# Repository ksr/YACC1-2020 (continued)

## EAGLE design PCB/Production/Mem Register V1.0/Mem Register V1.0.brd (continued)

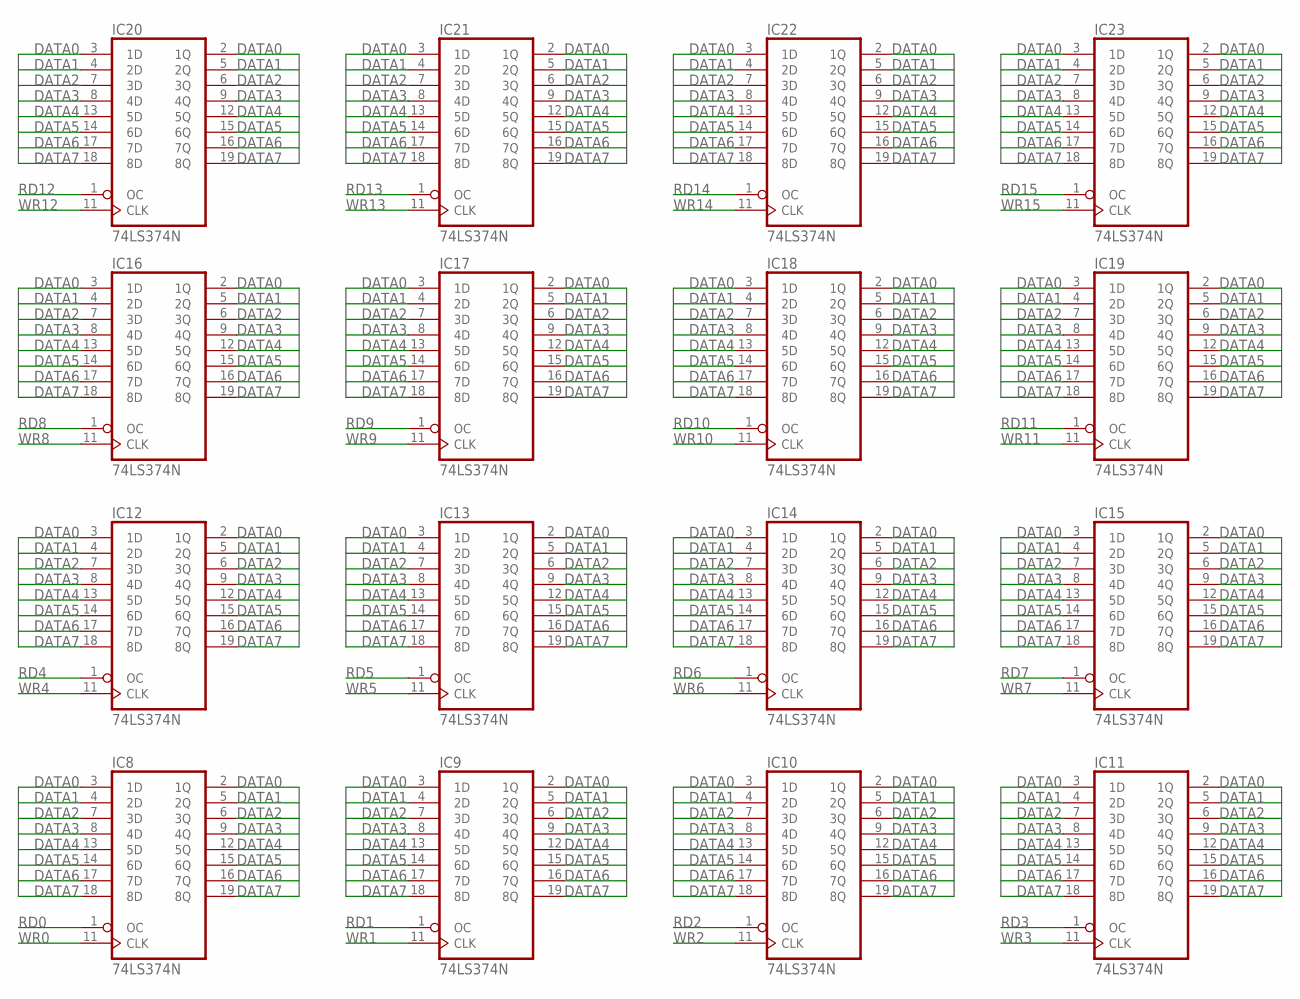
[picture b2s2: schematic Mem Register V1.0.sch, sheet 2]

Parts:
IC8, IC9, IC10, IC11, IC12, IC13, IC14, IC15, IC16, IC17, IC18, IC19, IC20, IC21, IC22, IC23: 74LS374N; DIL20

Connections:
DATA0: IC8.2 (1Q), IC8.3 (1D), IC9.2 (1Q), IC9.3 (1D), IC10.2 (1Q), IC10.3 (1D), IC11.2 (1Q), IC11.3 (1D), IC12.2 (1Q), IC12.3 (1D), IC13.2 (1Q), IC13.3 (1D), IC14.2 (1Q), IC14.3 (1D), IC15.2 (1Q), IC15.3 (1D), IC16.2 (1Q), IC16.3 (1D), IC17.2 (1Q), IC17.3 (1D), IC18.2 (1Q), IC18.3 (1D), IC19.2 (1Q), IC19.3 (1D), IC20.2 (1Q), IC20.3 (1D), IC21.2 (1Q), IC21.3 (1D), IC22.2 (1Q), IC22.3 (1D), IC23.2 (1Q), IC23.3 (1D); also elsewhere on the board
DATA1: IC8.4 (2D), IC8.5 (2Q), IC9.4 (2D), IC9.5 (2Q), IC10.4 (2D), IC10.5 (2Q), IC11.4 (2D), IC11.5 (2Q), IC12.4 (2D), IC12.5 (2Q), IC13.4 (2D), IC13.5 (2Q), IC14.4 (2D), IC14.5 (2Q), IC15.4 (2D), IC15.5 (2Q), IC16.4 (2D), IC16.5 (2Q), IC17.4 (2D), IC17.5 (2Q), IC18.4 (2D), IC18.5 (2Q), IC19.4 (2D), IC19.5 (2Q), IC20.4 (2D), IC20.5 (2Q), IC21.4 (2D), IC21.5 (2Q), IC22.4 (2D), IC22.5 (2Q), IC23.4 (2D), IC23.5 (2Q); also elsewhere on the board
DATA2: IC8.6 (3Q), IC8.7 (3D), IC9.6 (3Q), IC9.7 (3D), IC10.6 (3Q), IC10.7 (3D), IC11.6 (3Q), IC11.7 (3D), IC12.6 (3Q), IC12.7 (3D), IC13.6 (3Q), IC13.7 (3D), IC14.6 (3Q), IC14.7 (3D), IC15.6 (3Q), IC15.7 (3D), IC16.6 (3Q), IC16.7 (3D), IC17.6 (3Q), IC17.7 (3D), IC18.6 (3Q), IC18.7 (3D), IC19.6 (3Q), IC19.7 (3D), IC20.6 (3Q), IC20.7 (3D), IC21.6 (3Q), IC21.7 (3D), IC22.6 (3Q), IC22.7 (3D), IC23.6 (3Q), IC23.7 (3D); also elsewhere on the board
DATA3: IC8.8 (4D), IC8.9 (4Q), IC9.8 (4D), IC9.9 (4Q), IC10.8 (4D), IC10.9 (4Q), IC11.8 (4D), IC11.9 (4Q), IC12.8 (4D), IC12.9 (4Q), IC13.8 (4D), IC13.9 (4Q), IC14.8 (4D), IC14.9 (4Q), IC15.8 (4D), IC15.9 (4Q), IC16.8 (4D), IC16.9 (4Q), IC17.8 (4D), IC17.9 (4Q), IC18.8 (4D), IC18.9 (4Q), IC19.8 (4D), IC19.9 (4Q), IC20.8 (4D), IC20.9 (4Q), IC21.8 (4D), IC21.9 (4Q), IC22.8 (4D), IC22.9 (4Q), IC23.8 (4D), IC23.9 (4Q); also elsewhere on the board
DATA4: IC8.12 (5Q), IC8.13 (5D), IC9.12 (5Q), IC9.13 (5D), IC10.12 (5Q), IC10.13 (5D), IC11.12 (5Q), IC11.13 (5D), IC12.12 (5Q), IC12.13 (5D), IC13.12 (5Q), IC13.13 (5D), IC14.12 (5Q), IC14.13 (5D), IC15.12 (5Q), IC15.13 (5D), IC16.12 (5Q), IC16.13 (5D), IC17.12 (5Q), IC17.13 (5D), IC18.12 (5Q), IC18.13 (5D), IC19.12 (5Q), IC19.13 (5D), IC20.12 (5Q), IC20.13 (5D), IC21.12 (5Q), IC21.13 (5D), IC22.12 (5Q), IC22.13 (5D), IC23.12 (5Q), IC23.13 (5D); also elsewhere on the board
DATA5: IC8.14 (6D), IC8.15 (6Q), IC9.14 (6D), IC9.15 (6Q), IC10.14 (6D), IC10.15 (6Q), IC11.14 (6D), IC11.15 (6Q), IC12.14 (6D), IC12.15 (6Q), IC13.14 (6D), IC13.15 (6Q), IC14.14 (6D), IC14.15 (6Q), IC15.14 (6D), IC15.15 (6Q), IC16.14 (6D), IC16.15 (6Q), IC17.14 (6D), IC17.15 (6Q), IC18.14 (6D), IC18.15 (6Q), IC19.14 (6D), IC19.15 (6Q), IC20.14 (6D), IC20.15 (6Q), IC21.14 (6D), IC21.15 (6Q), IC22.14 (6D), IC22.15 (6Q), IC23.14 (6D), IC23.15 (6Q); also elsewhere on the board
DATA6: IC8.16 (7Q), IC8.17 (7D), IC9.16 (7Q), IC9.17 (7D), IC10.16 (7Q), IC10.17 (7D), IC11.16 (7Q), IC11.17 (7D), IC12.16 (7Q), IC12.17 (7D), IC13.16 (7Q), IC13.17 (7D), IC14.16 (7Q), IC14.17 (7D), IC15.16 (7Q), IC15.17 (7D), IC16.16 (7Q), IC16.17 (7D), IC17.16 (7Q), IC17.17 (7D), IC18.16 (7Q), IC18.17 (7D), IC19.16 (7Q), IC19.17 (7D), IC20.16 (7Q), IC20.17 (7D), IC21.16 (7Q), IC21.17 (7D), IC22.16 (7Q), IC22.17 (7D), IC23.16 (7Q), IC23.17 (7D); also elsewhere on the board
DATA7: IC8.18 (8D), IC8.19 (8Q), IC9.18 (8D), IC9.19 (8Q), IC10.18 (8D), IC10.19 (8Q), IC11.18 (8D), IC11.19 (8Q), IC12.18 (8D), IC12.19 (8Q), IC13.18 (8D), IC13.19 (8Q), IC14.18 (8D), IC14.19 (8Q), IC15.18 (8D), IC15.19 (8Q), IC16.18 (8D), IC16.19 (8Q), IC17.18 (8D), IC17.19 (8Q), IC18.18 (8D), IC18.19 (8Q), IC19.18 (8D), IC19.19 (8Q), IC20.18 (8D), IC20.19 (8Q), IC21.18 (8D), IC21.19 (8Q), IC22.18 (8D), IC22.19 (8Q), IC23.18 (8D), IC23.19 (8Q); also elsewhere on the board
GND: IC8.10 (GND), IC9.10 (GND), IC10.10 (GND), IC11.10 (GND), IC12.10 (GND), IC13.10 (GND), IC14.10 (GND), IC15.10 (GND), IC16.10 (GND), IC17.10 (GND), IC18.10 (GND), IC19.10 (GND), IC20.10 (GND), IC21.10 (GND), IC22.10 (GND), IC23.10 (GND); also elsewhere on the board
RD0: IC8.1 (OC); also elsewhere on the board
RD1: IC9.1 (OC); also elsewhere on the board
RD2: IC10.1 (OC); also elsewhere on the board
RD3: IC11.1 (OC); also elsewhere on the board
RD4: IC12.1 (OC); also elsewhere on the board
RD5: IC13.1 (OC); also elsewhere on the board
RD6: IC14.1 (OC); also elsewhere on the board
RD7: IC15.1 (OC); also elsewhere on the board
RD8: IC16.1 (OC); also elsewhere on the board
RD9: IC17.1 (OC); also elsewhere on the board
RD10: IC18.1 (OC); also elsewhere on the board
RD11: IC19.1 (OC); also elsewhere on the board
RD12: IC20.1 (OC); also elsewhere on the board
RD13: IC21.1 (OC); also elsewhere on the board
RD14: IC22.1 (OC); also elsewhere on the board
RD15: IC23.1 (OC); also elsewhere on the board
VCC: IC8.20 (VCC), IC9.20 (VCC), IC10.20 (VCC), IC11.20 (VCC), IC12.20 (VCC), IC13.20 (VCC), IC14.20 (VCC), IC15.20 (VCC), IC16.20 (VCC), IC17.20 (VCC), IC18.20 (VCC), IC19.20 (VCC), IC20.20 (VCC), IC21.20 (VCC), IC22.20 (VCC), IC23.20 (VCC); also elsewhere on the board
WR0: IC8.11 (CLK); also elsewhere on the board
WR1: IC9.11 (CLK); also elsewhere on the board
WR2: IC10.11 (CLK); also elsewhere on the board
WR3: IC11.11 (CLK); also elsewhere on the board
WR4: IC12.11 (CLK); also elsewhere on the board
WR5: IC13.11 (CLK); also elsewhere on the board
WR6: IC14.11 (CLK); also elsewhere on the board
WR7: IC15.11 (CLK); also elsewhere on the board
WR8: IC16.11 (CLK); also elsewhere on the board
WR9: IC17.11 (CLK); also elsewhere on the board
WR10: IC18.11 (CLK); also elsewhere on the board
WR11: IC19.11 (CLK); also elsewhere on the board
WR12: IC20.11 (CLK); also elsewhere on the board
WR13: IC21.11 (CLK); also elsewhere on the board
WR14: IC22.11 (CLK); also elsewhere on the board
WR15: IC23.11 (CLK); also elsewhere on the board

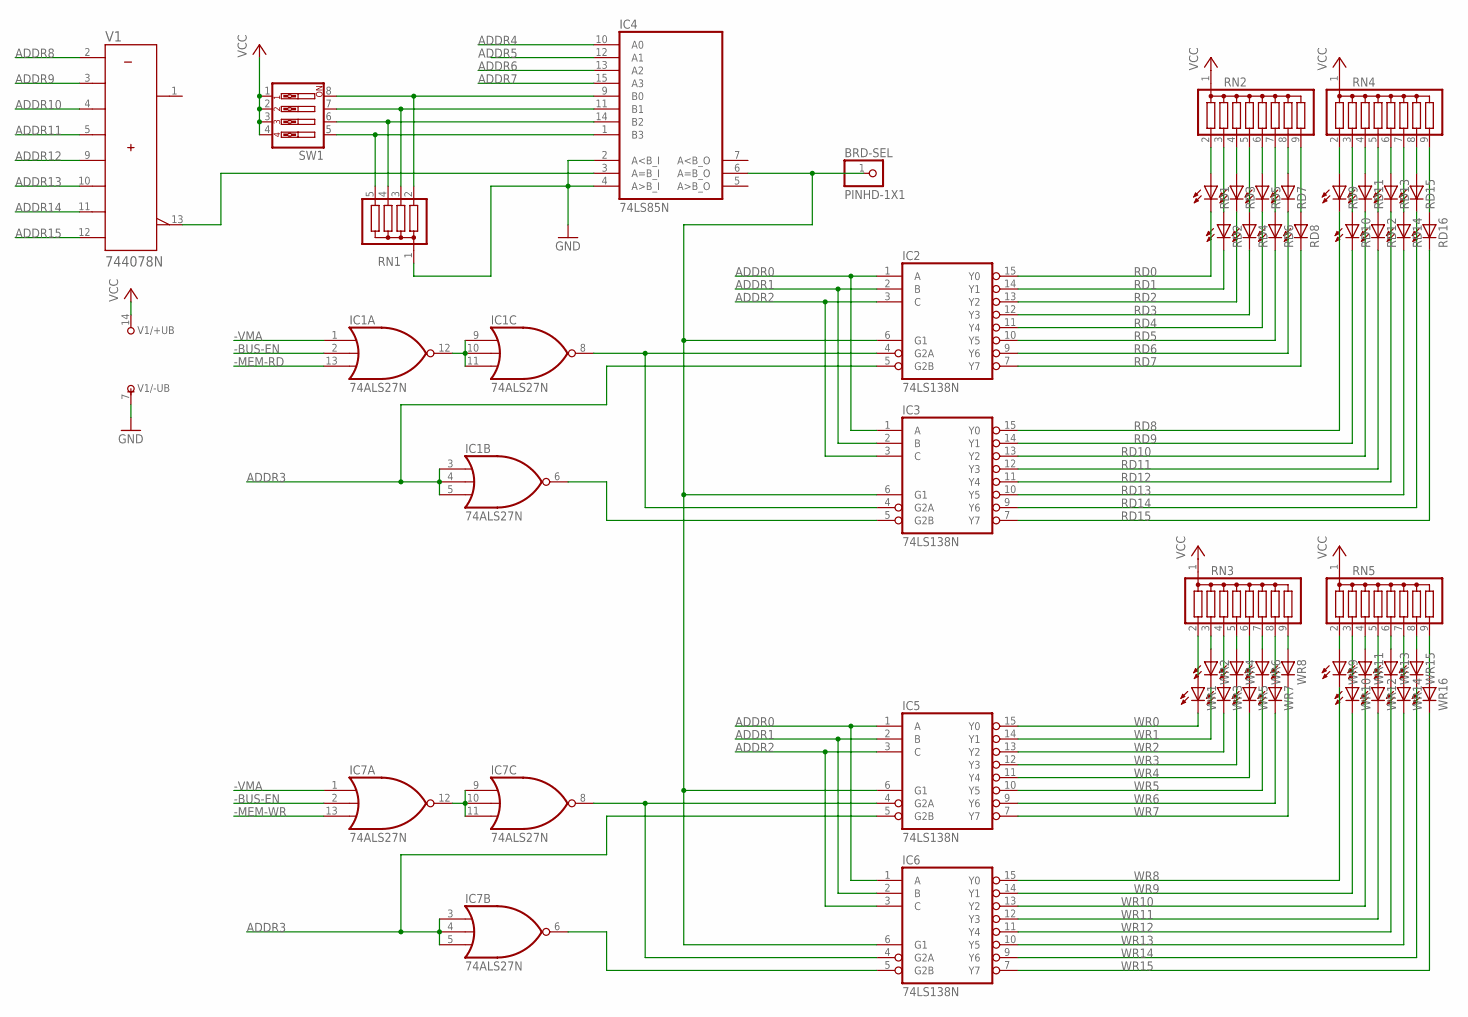
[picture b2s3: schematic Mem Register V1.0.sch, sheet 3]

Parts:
BRD-SEL: PINHD-1X1; 1X01
IC1, IC7: 74ALS27N; DIL14
IC2, IC3, IC5, IC6: 74LS138N; DIL16
IC4: 74LS85N; DIL16
RD1, RD2, RD3, RD4, RD5, RD6, RD7, RD8, RD9, RD10, RD11, RD12, RD13, RD14, RD15, RD16: LED3MM
RN1: G04R; SIL5
RN2, RN3, RN4, RN5: G08R; SIL9
SW1: SW_DIP-4; EDG-04
V1: 744078N; DIL14
WR1, WR2, WR3, WR4, WR5, WR6, WR7, WR8, WR9, WR10, WR11, WR12, WR13, WR14, WR15, WR16: LED3MM

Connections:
-BUS-EN: IC1.2 (I1), IC7.2 (I1); also elsewhere on the board
-MEM-RD: IC1.13 (I2); also elsewhere on the board
-MEM-WR: IC7.13 (I2); also elsewhere on the board
-VMA: IC1.1 (I0), IC7.1 (I0); also elsewhere on the board
ADDR0: IC2.1 (A), IC3.1 (A), IC5.1 (A), IC6.1 (A); also elsewhere on the board
ADDR1: IC2.2 (B), IC3.2 (B), IC5.2 (B), IC6.2 (B); also elsewhere on the board
ADDR2: IC2.3 (C), IC3.3 (C), IC5.3 (C), IC6.3 (C); also elsewhere on the board
ADDR3: IC1.3 (I0), IC1.4 (I1), IC1.5 (I2), IC2.5 (G2B), IC5.5 (G2B), IC7.3 (I0), IC7.4 (I1), IC7.5 (I2); also elsewhere on the board
ADDR4: IC4.10 (A0); also elsewhere on the board
ADDR5: IC4.12 (A1); also elsewhere on the board
ADDR6: IC4.13 (A2); also elsewhere on the board
ADDR7: IC4.15 (A3); also elsewhere on the board
ADDR8: V1.2 (A); also elsewhere on the board
ADDR9: V1.3 (B); also elsewhere on the board
ADDR10: V1.4 (C); also elsewhere on the board
ADDR11: V1.5 (D); also elsewhere on the board
ADDR12: V1.9 (E); also elsewhere on the board
ADDR13: V1.10 (F); also elsewhere on the board
ADDR14: V1.11 (G); also elsewhere on the board
ADDR15: V1.12 (H); also elsewhere on the board
GND: IC1.7 (GND), IC2.8 (GND), IC3.8 (GND), IC4.2 (A<B_I), IC4.4 (A>B_I), IC4.8 (GND), IC5.8 (GND), IC6.8 (GND), IC7.7 (GND), RN1.1, V1.7 (-UB); also elsewhere on the board
unnamed: RD1.A, RN2.2
unnamed: IC7.9 (I0), IC7.10 (I1), IC7.11 (I2), IC7.12 (O)
unnamed: IC6.5 (G2B), IC7.6 (O)
unnamed: IC5.4 (G2A), IC6.4 (G2A), IC7.8 (O)
unnamed: RD3.A, RN2.4
unnamed: BRD-SEL.1, IC2.6 (G1), IC3.6 (G1), IC4.6 (A=B_O), IC5.6 (G1), IC6.6 (G1)
unnamed: RD2.A, RN2.3
unnamed: IC4.3 (A=B_I), V1.13 (W)
unnamed: RD9.A, RN4.2
unnamed: RD4.A, RN2.5
unnamed: RD5.A, RN2.6
unnamed: RD7.A, RN2.8
unnamed: RD8.A, RN2.9
unnamed: RD6.A, RN2.7
unnamed: RD10.A, RN4.3
unnamed: RD11.A, RN4.4
unnamed: RD12.A, RN4.5
unnamed: IC1.9 (I0), IC1.10 (I1), IC1.11 (I2), IC1.12 (O)
unnamed: RD13.A, RN4.6
unnamed: RD14.A, RN4.7
unnamed: RD15.A, RN4.8
unnamed: RD16.A, RN4.9
unnamed: RN3.2, WR1.A
unnamed: RN3.3, WR2.A
unnamed: RN3.4, WR3.A
unnamed: RN3.5, WR4.A
unnamed: IC4.9 (B0), RN1.2, SW1.8
unnamed: RN3.7, WR6.A
unnamed: RN3.6, WR5.A
unnamed: RN3.8, WR7.A
unnamed: RN3.9, WR8.A
unnamed: RN5.2, WR9.A
unnamed: RN5.4, WR11.A
unnamed: RN5.6, WR13.A
unnamed: RN5.8, WR15.A
unnamed: IC1.6 (O), IC3.5 (G2B)
unnamed: RN5.9, WR16.A
unnamed: RN5.7, WR14.A
unnamed: RN5.5, WR12.A
unnamed: RN5.3, WR10.A
unnamed: IC4.11 (B1), RN1.3, SW1.7
unnamed: IC4.14 (B2), RN1.4, SW1.6
unnamed: IC4.1 (B3), RN1.5, SW1.5
unnamed: IC1.8 (O), IC2.4 (G2A), IC3.4 (G2A)
RD0: IC2.15 (Y0), RD1.K (C); also elsewhere on the board
RD1: IC2.14 (Y1), RD2.K (C); also elsewhere on the board
RD2: IC2.13 (Y2), RD3.K (C); also elsewhere on the board
RD3: IC2.12 (Y3), RD4.K (C); also elsewhere on the board
RD4: IC2.11 (Y4), RD5.K (C); also elsewhere on the board
RD5: IC2.10 (Y5), RD6.K (C); also elsewhere on the board
RD6: IC2.9 (Y6), RD7.K (C); also elsewhere on the board
RD7: IC2.7 (Y7), RD8.K (C); also elsewhere on the board
RD8: IC3.15 (Y0), RD9.K (C); also elsewhere on the board
RD9: IC3.14 (Y1), RD10.K (C); also elsewhere on the board
RD10: IC3.13 (Y2), RD11.K (C); also elsewhere on the board
RD11: IC3.12 (Y3), RD12.K (C); also elsewhere on the board
RD12: IC3.11 (Y4), RD13.K (C); also elsewhere on the board
RD13: IC3.10 (Y5), RD14.K (C); also elsewhere on the board
RD14: IC3.9 (Y6), RD15.K (C); also elsewhere on the board
RD15: IC3.7 (Y7), RD16.K (C); also elsewhere on the board
VCC: IC1.14 (VCC), IC2.16 (VCC), IC3.16 (VCC), IC4.16 (VCC), IC5.16 (VCC), IC6.16 (VCC), IC7.14 (VCC), RN2.1, RN3.1, RN4.1, RN5.1, SW1.1, SW1.2, SW1.3, SW1.4, V1.14 (+UB); also elsewhere on the board
WR0: IC5.15 (Y0), WR1.K (C); also elsewhere on the board
WR1: IC5.14 (Y1), WR2.K (C); also elsewhere on the board
WR2: IC5.13 (Y2), WR3.K (C); also elsewhere on the board
WR3: IC5.12 (Y3), WR4.K (C); also elsewhere on the board
WR4: IC5.11 (Y4), WR5.K (C); also elsewhere on the board
WR5: IC5.10 (Y5), WR6.K (C); also elsewhere on the board
WR6: IC5.9 (Y6), WR7.K (C); also elsewhere on the board
WR7: IC5.7 (Y7), WR8.K (C); also elsewhere on the board
WR8: IC6.15 (Y0), WR9.K (C); also elsewhere on the board
WR9: IC6.14 (Y1), WR10.K (C); also elsewhere on the board
WR10: IC6.13 (Y2), WR11.K (C); also elsewhere on the board
WR11: IC6.12 (Y3), WR12.K (C); also elsewhere on the board
WR12: IC6.11 (Y4), WR13.K (C); also elsewhere on the board
WR13: IC6.10 (Y5), WR14.K (C); also elsewhere on the board
WR14: IC6.9 (Y6), WR15.K (C); also elsewhere on the board
WR15: IC6.7 (Y7), WR16.K (C); also elsewhere on the board

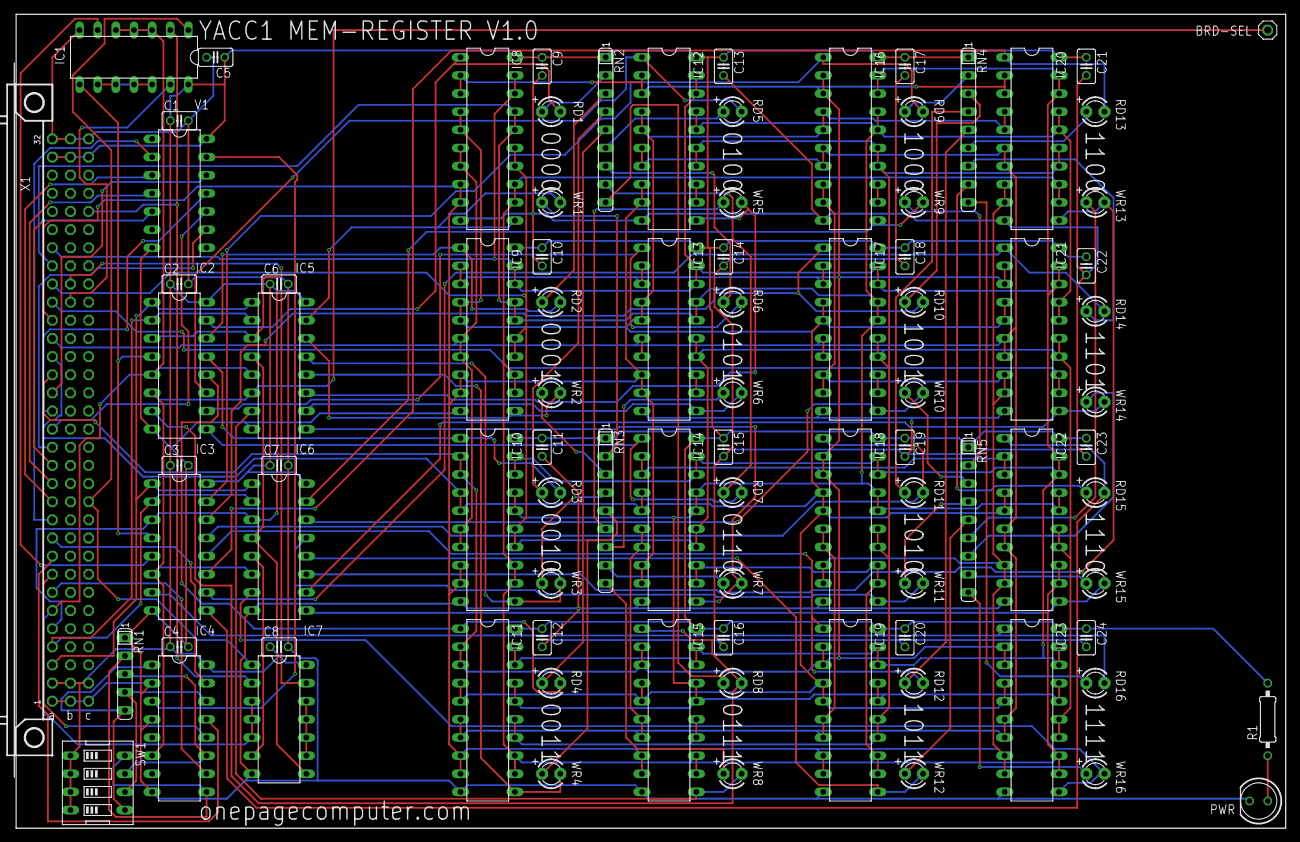
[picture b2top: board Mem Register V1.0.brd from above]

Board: 2 copper layers, 177.8 x 114.0 mm, 90 parts (0 on the bottom side), 107 nets.

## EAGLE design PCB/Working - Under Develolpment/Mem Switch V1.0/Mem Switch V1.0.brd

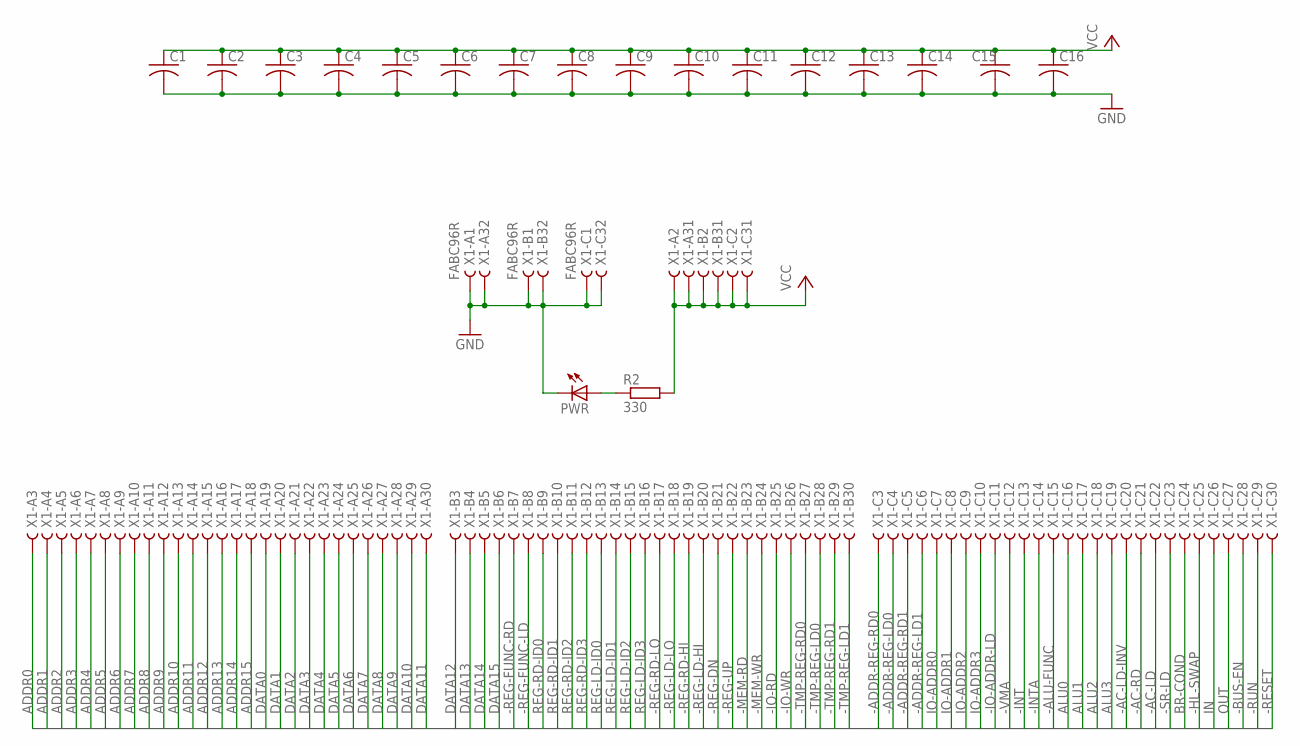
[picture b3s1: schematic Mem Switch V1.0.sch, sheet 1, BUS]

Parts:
C1, C2, C3, C4, C5, C6, C7, C8, C9, C10, C11, C12, C13, C14, C15, C16: C-US025-025X050; C025-025X050
PWR: LED5MM
R2: 330; 0207/10
X1: FABC96R

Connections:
-AC-LD: X1.C22
-AC-LD-INV: X1.C20
-AC-RD: X1.C21
-ADDR-REG-LD0: X1.C4
-ADDR-REG-LD1: X1.C6
-ADDR-REG-RD0: X1.C3
-ADDR-REG-RD1: X1.C5
-ALU-FUNC: X1.C15
-BUS-EN: X1.C28; also elsewhere on the board
-HL-SWAP: X1.C25
-INT: X1.C13
-INTA: X1.C14
-IO-ADDR-LD: X1.C11
-IO-RD: X1.B25
-IO-WR: X1.B26
-MEM-RD: X1.B23; also elsewhere on the board
-MEM-WR: X1.B24
-REG-DN: X1.B21
-REG-FUNC-LD: X1.B8
-REG-FUNC-RD: X1.B7
-REG-LD-HI: X1.B20
-REG-LD-LO: X1.B18
-REG-RD-HI: X1.B19
-REG-RD-LO: X1.B17
-REG-UP: X1.B22
-RESET: X1.C30
-RUN: X1.C29
-SR-LD: X1.C23
-TMP-REG-LD0: X1.B28
-TMP-REG-LD1: X1.B30
-TMP-REG-RD0: X1.B27
-TMP-REG-RD1: X1.B29
-VMA: X1.C12; also elsewhere on the board
ADDR0: X1.A3; also elsewhere on the board
ADDR1: X1.A4; also elsewhere on the board
ADDR2: X1.A5; also elsewhere on the board
ADDR3: X1.A6; also elsewhere on the board
ADDR4: X1.A7; also elsewhere on the board
ADDR5: X1.A8; also elsewhere on the board
ADDR6: X1.A9
ADDR7: X1.A10
ADDR8: X1.A11; also elsewhere on the board
ADDR9: X1.A12; also elsewhere on the board
ADDR10: X1.A13; also elsewhere on the board
ADDR11: X1.A14; also elsewhere on the board
ADDR12: X1.A15; also elsewhere on the board
ADDR13: X1.A16; also elsewhere on the board
ADDR14: X1.A17; also elsewhere on the board
ADDR15: X1.A18; also elsewhere on the board
ALU0: X1.C16
ALU1: X1.C17
ALU2: X1.C18
ALU3: X1.C19
BR-COND: X1.C24
DATA0: X1.A19; also elsewhere on the board
DATA1: X1.A20; also elsewhere on the board
DATA2: X1.A21; also elsewhere on the board
DATA3: X1.A22; also elsewhere on the board
DATA4: X1.A23; also elsewhere on the board
DATA5: X1.A24; also elsewhere on the board
DATA6: X1.A25; also elsewhere on the board
DATA7: X1.A26; also elsewhere on the board
DATA8: X1.A27
DATA9: X1.A28
DATA10: X1.A29
DATA11: X1.A30
DATA12: X1.B3
DATA13: X1.B4
DATA14: X1.B5
DATA15: X1.B6
GND: C1.2, C2.2, C3.2, C4.2, C5.2, C6.2, C7.2, C8.2, C9.2, C10.2, C11.2, C12.2, C13.2, C14.2, C15.2, C16.2, PWR.K (C), X1.A1, X1.A32, X1.B1, X1.B32, X1.C1, X1.C32; also elsewhere on the board
IN: X1.C26
IO-ADDR0: X1.C7
IO-ADDR1: X1.C8
IO-ADDR2: X1.C9
IO-ADDR3: X1.C10
unnamed: PWR.A, R2.1
OUT: X1.C27
REG-LD-ID0: X1.B13
REG-LD-ID1: X1.B14
REG-LD-ID2: X1.B15
REG-LD-ID3: X1.B16
REG-RD-ID0: X1.B9
REG-RD-ID1: X1.B10
REG-RD-ID2: X1.B11
REG-RD-ID3: X1.B12
VCC: C1.1, C2.1, C3.1, C4.1, C5.1, C6.1, C7.1, C8.1, C9.1, C10.1, C11.1, C12.1, C13.1, C14.1, C15.1, C16.1, R2.2, X1.A2, X1.A31, X1.B2, X1.B31, X1.C2, X1.C31; also elsewhere on the board

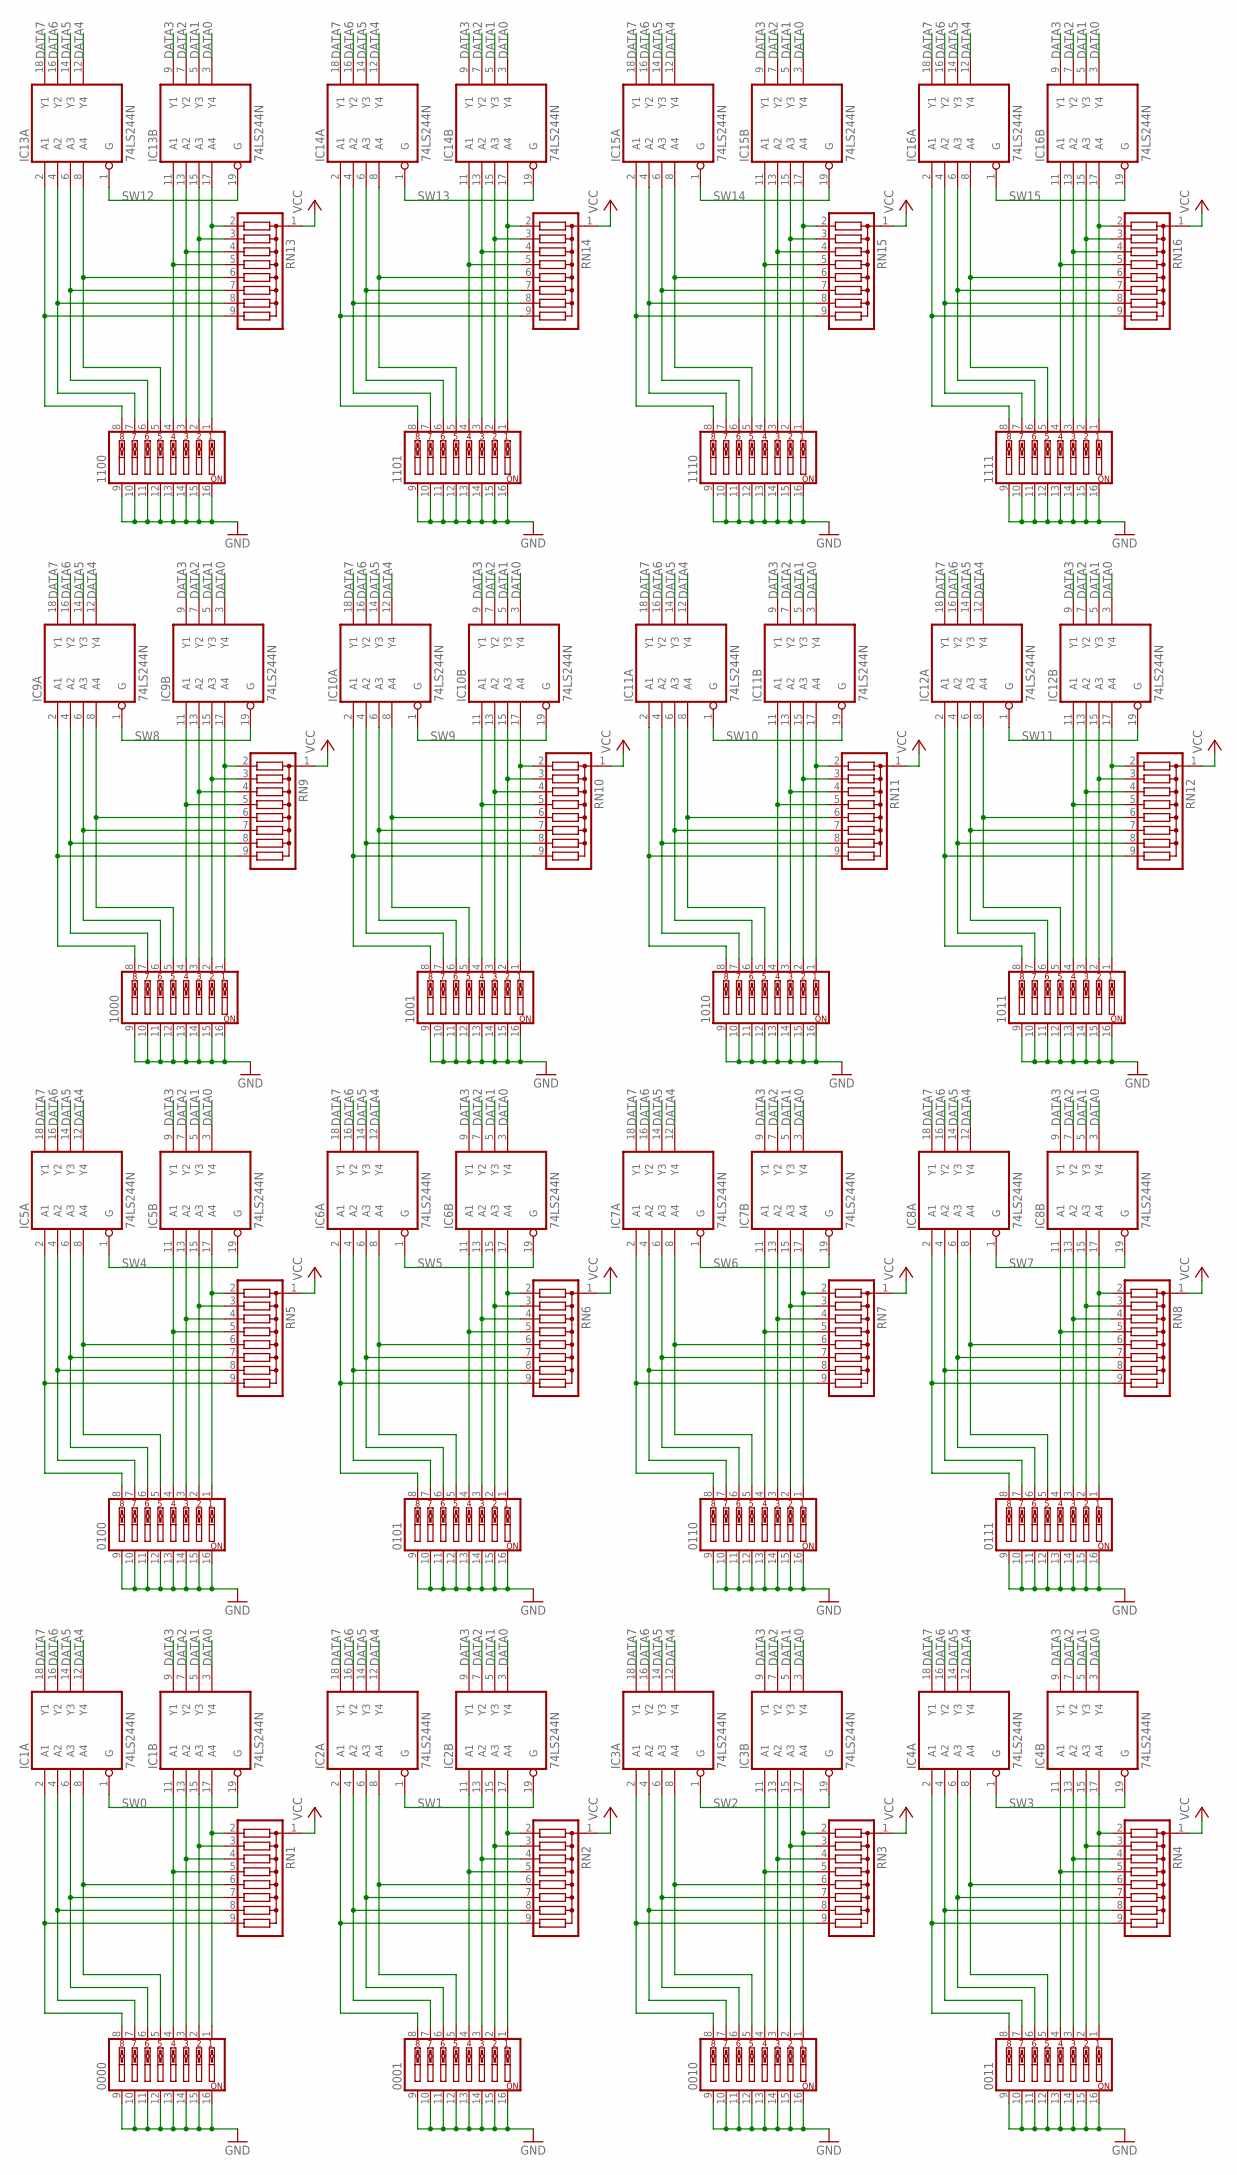
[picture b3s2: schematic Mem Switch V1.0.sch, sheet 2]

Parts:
0000, 0001, 0010, 0011, 0100, 0101, 0110, 0111, 1000, 1001, 1010, 1011, 1100, 1101, 1110, 1111: SW_DIP-8; EDG-08
IC1, IC2, IC3, IC4, IC5, IC6, IC7, IC8, IC9, IC10, IC11, IC12, IC13, IC14, IC15, IC16: 74LS244N; DIL20
RN1, RN2, RN3, RN4, RN5, RN6, RN7, RN8, RN9, RN10, RN11, RN12, RN13, RN14, RN15, RN16: G08R; SIL9

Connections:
DATA0: IC1.3 (Y4), IC2.3 (Y4), IC3.3 (Y4), IC4.3 (Y4), IC5.3 (Y4), IC6.3 (Y4), IC7.3 (Y4), IC8.3 (Y4), IC9.3 (Y4), IC10.3 (Y4), IC11.3 (Y4), IC12.3 (Y4), IC13.3 (Y4), IC14.3 (Y4), IC15.3 (Y4), IC16.3 (Y4); also elsewhere on the board
DATA1: IC1.5 (Y3), IC2.5 (Y3), IC3.5 (Y3), IC4.5 (Y3), IC5.5 (Y3), IC6.5 (Y3), IC7.5 (Y3), IC8.5 (Y3), IC9.5 (Y3), IC10.5 (Y3), IC11.5 (Y3), IC12.5 (Y3), IC13.5 (Y3), IC14.5 (Y3), IC15.5 (Y3), IC16.5 (Y3); also elsewhere on the board
DATA2: IC1.7 (Y2), IC2.7 (Y2), IC3.7 (Y2), IC4.7 (Y2), IC5.7 (Y2), IC6.7 (Y2), IC7.7 (Y2), IC8.7 (Y2), IC9.7 (Y2), IC10.7 (Y2), IC11.7 (Y2), IC12.7 (Y2), IC13.7 (Y2), IC14.7 (Y2), IC15.7 (Y2), IC16.7 (Y2); also elsewhere on the board
DATA3: IC1.9 (Y1), IC2.9 (Y1), IC3.9 (Y1), IC4.9 (Y1), IC5.9 (Y1), IC6.9 (Y1), IC7.9 (Y1), IC8.9 (Y1), IC9.9 (Y1), IC10.9 (Y1), IC11.9 (Y1), IC12.9 (Y1), IC13.9 (Y1), IC14.9 (Y1), IC15.9 (Y1), IC16.9 (Y1); also elsewhere on the board
DATA4: IC1.12 (Y4), IC2.12 (Y4), IC3.12 (Y4), IC4.12 (Y4), IC5.12 (Y4), IC6.12 (Y4), IC7.12 (Y4), IC8.12 (Y4), IC9.12 (Y4), IC10.12 (Y4), IC11.12 (Y4), IC12.12 (Y4), IC13.12 (Y4), IC14.12 (Y4), IC15.12 (Y4), IC16.12 (Y4); also elsewhere on the board
DATA5: IC1.14 (Y3), IC2.14 (Y3), IC3.14 (Y3), IC4.14 (Y3), IC5.14 (Y3), IC6.14 (Y3), IC7.14 (Y3), IC8.14 (Y3), IC9.14 (Y3), IC10.14 (Y3), IC11.14 (Y3), IC12.14 (Y3), IC13.14 (Y3), IC14.14 (Y3), IC15.14 (Y3), IC16.14 (Y3); also elsewhere on the board
DATA6: IC1.16 (Y2), IC2.16 (Y2), IC3.16 (Y2), IC4.16 (Y2), IC5.16 (Y2), IC6.16 (Y2), IC7.16 (Y2), IC8.16 (Y2), IC9.16 (Y2), IC10.16 (Y2), IC11.16 (Y2), IC12.16 (Y2), IC13.16 (Y2), IC14.16 (Y2), IC15.16 (Y2), IC16.16 (Y2); also elsewhere on the board
DATA7: IC1.18 (Y1), IC2.18 (Y1), IC3.18 (Y1), IC4.18 (Y1), IC5.18 (Y1), IC6.18 (Y1), IC7.18 (Y1), IC8.18 (Y1), IC9.18 (Y1), IC10.18 (Y1), IC11.18 (Y1), IC12.18 (Y1), IC13.18 (Y1), IC14.18 (Y1), IC15.18 (Y1), IC16.18 (Y1); also elsewhere on the board
GND: 0000.9, 0000.10, 0000.11, 0000.12, 0000.13, 0000.14, 0000.15, 0000.16, 0001.9, 0001.10, 0001.11, 0001.12, 0001.13, 0001.14, 0001.15, 0001.16, 0010.9, 0010.10, 0010.11, 0010.12, 0010.13, 0010.14, 0010.15, 0010.16, 0011.9, 0011.10, 0011.11, 0011.12, 0011.13, 0011.14, 0011.15, 0011.16, 0100.9, 0100.10, 0100.11, 0100.12, 0100.13, 0100.14, 0100.15, 0100.16, 0101.9, 0101.10, 0101.11, 0101.12, 0101.13, 0101.14, 0101.15, 0101.16, 0110.9, 0110.10, 0110.11, 0110.12, 0110.13, 0110.14, 0110.15, 0110.16, 0111.9, 0111.10, 0111.11, 0111.12, 0111.13, 0111.14, 0111.15, 0111.16, 1000.9, 1000.10, 1000.11, 1000.12, 1000.13, 1000.14, 1000.15, 1000.16, 1001.9, 1001.10, 1001.11, 1001.12, 1001.13, 1001.14, 1001.15, 1001.16, 1010.9, 1010.10, 1010.11, 1010.12, 1010.13, 1010.14, 1010.15, 1010.16, 1011.9, 1011.10, 1011.11, 1011.12, 1011.13, 1011.14, 1011.15, 1011.16, 1100.9, 1100.10, 1100.11, 1100.12, 1100.13, 1100.14, 1100.15, 1100.16, 1101.9, 1101.10, 1101.11, 1101.12, 1101.13, 1101.14, 1101.15, 1101.16, 1110.9, 1110.10, 1110.11, 1110.12, 1110.13, 1110.14, 1110.15, 1110.16, 1111.9, 1111.10, 1111.11, 1111.12, 1111.13, 1111.14, 1111.15, 1111.16, IC1.10 (GND), IC2.10 (GND), IC3.10 (GND), IC4.10 (GND), IC5.10 (GND), IC6.10 (GND), IC7.10 (GND), IC8.10 (GND), IC9.10 (GND), IC10.10 (GND), IC11.10 (GND), IC12.10 (GND), IC13.10 (GND), IC14.10 (GND), IC15.10 (GND), IC16.10 (GND); also elsewhere on the board
unnamed: 0000.1, IC1.17 (A4), RN1.2
unnamed: 0000.2, IC1.15 (A3), RN1.3
unnamed: 0000.3, IC1.13 (A2), RN1.4
unnamed: 0000.4, IC1.11 (A1), RN1.5
unnamed: 0000.5, IC1.8 (A4), RN1.6
unnamed: 0000.6, IC1.6 (A3), RN1.7
unnamed: 0000.7, IC1.4 (A2), RN1.8
unnamed: 0000.8, IC1.2 (A1), RN1.9
unnamed: 0001.1, IC2.17 (A4), RN2.2
unnamed: 0001.2, IC2.15 (A3), RN2.3
unnamed: 0001.3, IC2.13 (A2), RN2.4
unnamed: 0001.4, IC2.11 (A1), RN2.5
unnamed: 0001.5, IC2.8 (A4), RN2.6
unnamed: 0001.6, IC2.6 (A3), RN2.7
unnamed: 0001.7, IC2.4 (A2), RN2.8
unnamed: 0001.8, IC2.2 (A1), RN2.9
unnamed: 0010.1, IC3.17 (A4), RN3.2
unnamed: 0010.2, IC3.15 (A3), RN3.3
unnamed: 0010.3, IC3.13 (A2), RN3.4
unnamed: 0010.4, IC3.11 (A1), RN3.5
unnamed: 0010.5, IC3.8 (A4), RN3.6
unnamed: 0010.6, IC3.6 (A3), RN3.7
unnamed: 0010.7, IC3.4 (A2), RN3.8
unnamed: 0010.8, IC3.2 (A1), RN3.9
unnamed: 0011.1, IC4.17 (A4), RN4.2
unnamed: 0011.2, IC4.15 (A3), RN4.3
unnamed: 0011.3, IC4.13 (A2), RN4.4
unnamed: 0011.4, IC4.11 (A1), RN4.5
unnamed: 0011.5, IC4.8 (A4), RN4.6
unnamed: 0011.6, IC4.6 (A3), RN4.7
unnamed: 0011.7, IC4.4 (A2), RN4.8
unnamed: 0011.8, IC4.2 (A1), RN4.9
unnamed: 0100.1, IC5.17 (A4), RN5.2
unnamed: 0100.2, IC5.15 (A3), RN5.3
unnamed: 0100.3, IC5.13 (A2), RN5.4
unnamed: 0100.4, IC5.11 (A1), RN5.5
unnamed: 0100.5, IC5.8 (A4), RN5.6
unnamed: 0100.6, IC5.6 (A3), RN5.7
unnamed: 0100.7, IC5.4 (A2), RN5.8
unnamed: 0100.8, IC5.2 (A1), RN5.9
unnamed: 0101.1, IC6.17 (A4), RN6.2
unnamed: 0101.2, IC6.15 (A3), RN6.3
unnamed: 0101.3, IC6.13 (A2), RN6.4
unnamed: 0101.4, IC6.11 (A1), RN6.5
unnamed: 0101.5, IC6.8 (A4), RN6.6
unnamed: 0101.6, IC6.6 (A3), RN6.7
unnamed: 0101.7, IC6.4 (A2), RN6.8
unnamed: 0101.8, IC6.2 (A1), RN6.9
unnamed: 0110.1, IC7.17 (A4), RN7.2
unnamed: 0110.2, IC7.15 (A3), RN7.3
unnamed: 0110.3, IC7.13 (A2), RN7.4
unnamed: 0110.4, IC7.11 (A1), RN7.5
unnamed: 0110.5, IC7.8 (A4), RN7.6
unnamed: 0110.6, IC7.6 (A3), RN7.7
unnamed: 0110.7, IC7.4 (A2), RN7.8
unnamed: 0110.8, IC7.2 (A1), RN7.9
unnamed: 0111.1, IC8.17 (A4), RN8.2
unnamed: 0111.2, IC8.15 (A3), RN8.3
unnamed: 0111.3, IC8.13 (A2), RN8.4
unnamed: 0111.4, IC8.11 (A1), RN8.5
unnamed: 0111.5, IC8.8 (A4), RN8.6
unnamed: 0111.6, IC8.6 (A3), RN8.7
unnamed: 0111.7, IC8.4 (A2), RN8.8
unnamed: 0111.8, IC8.2 (A1), RN8.9
unnamed: 1000.1, IC9.17 (A4), RN9.2
unnamed: 1000.2, IC9.15 (A3), RN9.3
unnamed: 1000.3, IC9.13 (A2), RN9.4
unnamed: 1000.4, IC9.11 (A1), RN9.5
unnamed: 1000.5, IC9.8 (A4), RN9.6
unnamed: 1000.6, IC9.6 (A3), RN9.7
unnamed: 1000.7, IC9.4 (A2), RN9.8
unnamed: 1000.8, IC9.2 (A1), RN9.9
unnamed: 1001.1, IC10.17 (A4), RN10.2
unnamed: 1001.2, IC10.15 (A3), RN10.3
unnamed: 1001.3, IC10.13 (A2), RN10.4
unnamed: 1001.4, IC10.11 (A1), RN10.5
unnamed: 1001.5, IC10.8 (A4), RN10.6
unnamed: 1001.6, IC10.6 (A3), RN10.7
unnamed: 1001.7, IC10.4 (A2), RN10.8
unnamed: 1001.8, IC10.2 (A1), RN10.9
unnamed: 1010.1, IC11.17 (A4), RN11.2
unnamed: 1010.2, IC11.15 (A3), RN11.3
unnamed: 1010.3, IC11.13 (A2), RN11.4
unnamed: 1010.4, IC11.11 (A1), RN11.5
unnamed: 1010.5, IC11.8 (A4), RN11.6
unnamed: 1010.6, IC11.6 (A3), RN11.7
unnamed: 1010.7, IC11.4 (A2), RN11.8
unnamed: 1010.8, IC11.2 (A1), RN11.9
unnamed: 1011.1, IC12.17 (A4), RN12.2
unnamed: 1011.2, IC12.15 (A3), RN12.3
unnamed: 1011.3, IC12.13 (A2), RN12.4
unnamed: 1011.4, IC12.11 (A1), RN12.5
unnamed: 1011.5, IC12.8 (A4), RN12.6
unnamed: 1011.6, IC12.6 (A3), RN12.7
unnamed: 1011.7, IC12.4 (A2), RN12.8
unnamed: 1011.8, IC12.2 (A1), RN12.9
unnamed: 1100.1, IC13.17 (A4), RN13.2
unnamed: 1100.2, IC13.15 (A3), RN13.3
unnamed: 1100.3, IC13.13 (A2), RN13.4
unnamed: 1100.4, IC13.11 (A1), RN13.5
unnamed: 1100.5, IC13.8 (A4), RN13.6
unnamed: 1100.6, IC13.6 (A3), RN13.7
unnamed: 1100.7, IC13.4 (A2), RN13.8
unnamed: 1100.8, IC13.2 (A1), RN13.9
unnamed: 1101.1, IC14.17 (A4), RN14.2
unnamed: 1101.2, IC14.15 (A3), RN14.3
unnamed: 1101.3, IC14.13 (A2), RN14.4
unnamed: 1101.4, IC14.11 (A1), RN14.5
unnamed: 1101.5, IC14.8 (A4), RN14.6
unnamed: 1101.6, IC14.6 (A3), RN14.7
unnamed: 1101.7, IC14.4 (A2), RN14.8
unnamed: 1101.8, IC14.2 (A1), RN14.9
unnamed: 1110.1, IC15.17 (A4), RN15.2
unnamed: 1110.2, IC15.15 (A3), RN15.3
unnamed: 1110.3, IC15.13 (A2), RN15.4
unnamed: 1110.4, IC15.11 (A1), RN15.5
unnamed: 1110.5, IC15.8 (A4), RN15.6
unnamed: 1110.6, IC15.6 (A3), RN15.7
unnamed: 1110.7, IC15.4 (A2), RN15.8
unnamed: 1110.8, IC15.2 (A1), RN15.9
unnamed: 1111.1, IC16.17 (A4), RN16.2
unnamed: 1111.2, IC16.15 (A3), RN16.3
unnamed: 1111.3, IC16.13 (A2), RN16.4
unnamed: 1111.4, IC16.11 (A1), RN16.5
unnamed: 1111.5, IC16.8 (A4), RN16.6
unnamed: 1111.6, IC16.6 (A3), RN16.7
unnamed: 1111.7, IC16.4 (A2), RN16.8
unnamed: 1111.8, IC16.2 (A1), RN16.9
SW0: IC1.1 (G), IC1.19 (G); also elsewhere on the board
SW1: IC2.1 (G), IC2.19 (G); also elsewhere on the board
SW2: IC3.1 (G), IC3.19 (G); also elsewhere on the board
SW3: IC4.1 (G), IC4.19 (G); also elsewhere on the board
SW4: IC5.1 (G), IC5.19 (G); also elsewhere on the board
SW5: IC6.1 (G), IC6.19 (G); also elsewhere on the board
SW6: IC7.1 (G), IC7.19 (G); also elsewhere on the board
SW7: IC8.1 (G), IC8.19 (G); also elsewhere on the board
SW8: IC9.1 (G), IC9.19 (G); also elsewhere on the board
SW9: IC10.1 (G), IC10.19 (G); also elsewhere on the board
SW10: IC11.1 (G), IC11.19 (G); also elsewhere on the board
SW11: IC12.1 (G), IC12.19 (G); also elsewhere on the board
SW12: IC13.1 (G), IC13.19 (G); also elsewhere on the board
SW13: IC14.1 (G), IC14.19 (G); also elsewhere on the board
SW14: IC15.1 (G), IC15.19 (G); also elsewhere on the board
SW15: IC16.1 (G), IC16.19 (G); also elsewhere on the board
VCC: IC1.20 (VCC), IC2.20 (VCC), IC3.20 (VCC), IC4.20 (VCC), IC5.20 (VCC), IC6.20 (VCC), IC7.20 (VCC), IC8.20 (VCC), IC9.20 (VCC), IC10.20 (VCC), IC11.20 (VCC), IC12.20 (VCC), IC13.20 (VCC), IC14.20 (VCC), IC15.20 (VCC), IC16.20 (VCC), RN1.1, RN2.1, RN3.1, RN4.1, RN5.1, RN6.1, RN7.1, RN8.1, RN9.1, RN10.1, RN11.1, RN12.1, RN13.1, RN14.1, RN15.1, RN16.1; also elsewhere on the board
